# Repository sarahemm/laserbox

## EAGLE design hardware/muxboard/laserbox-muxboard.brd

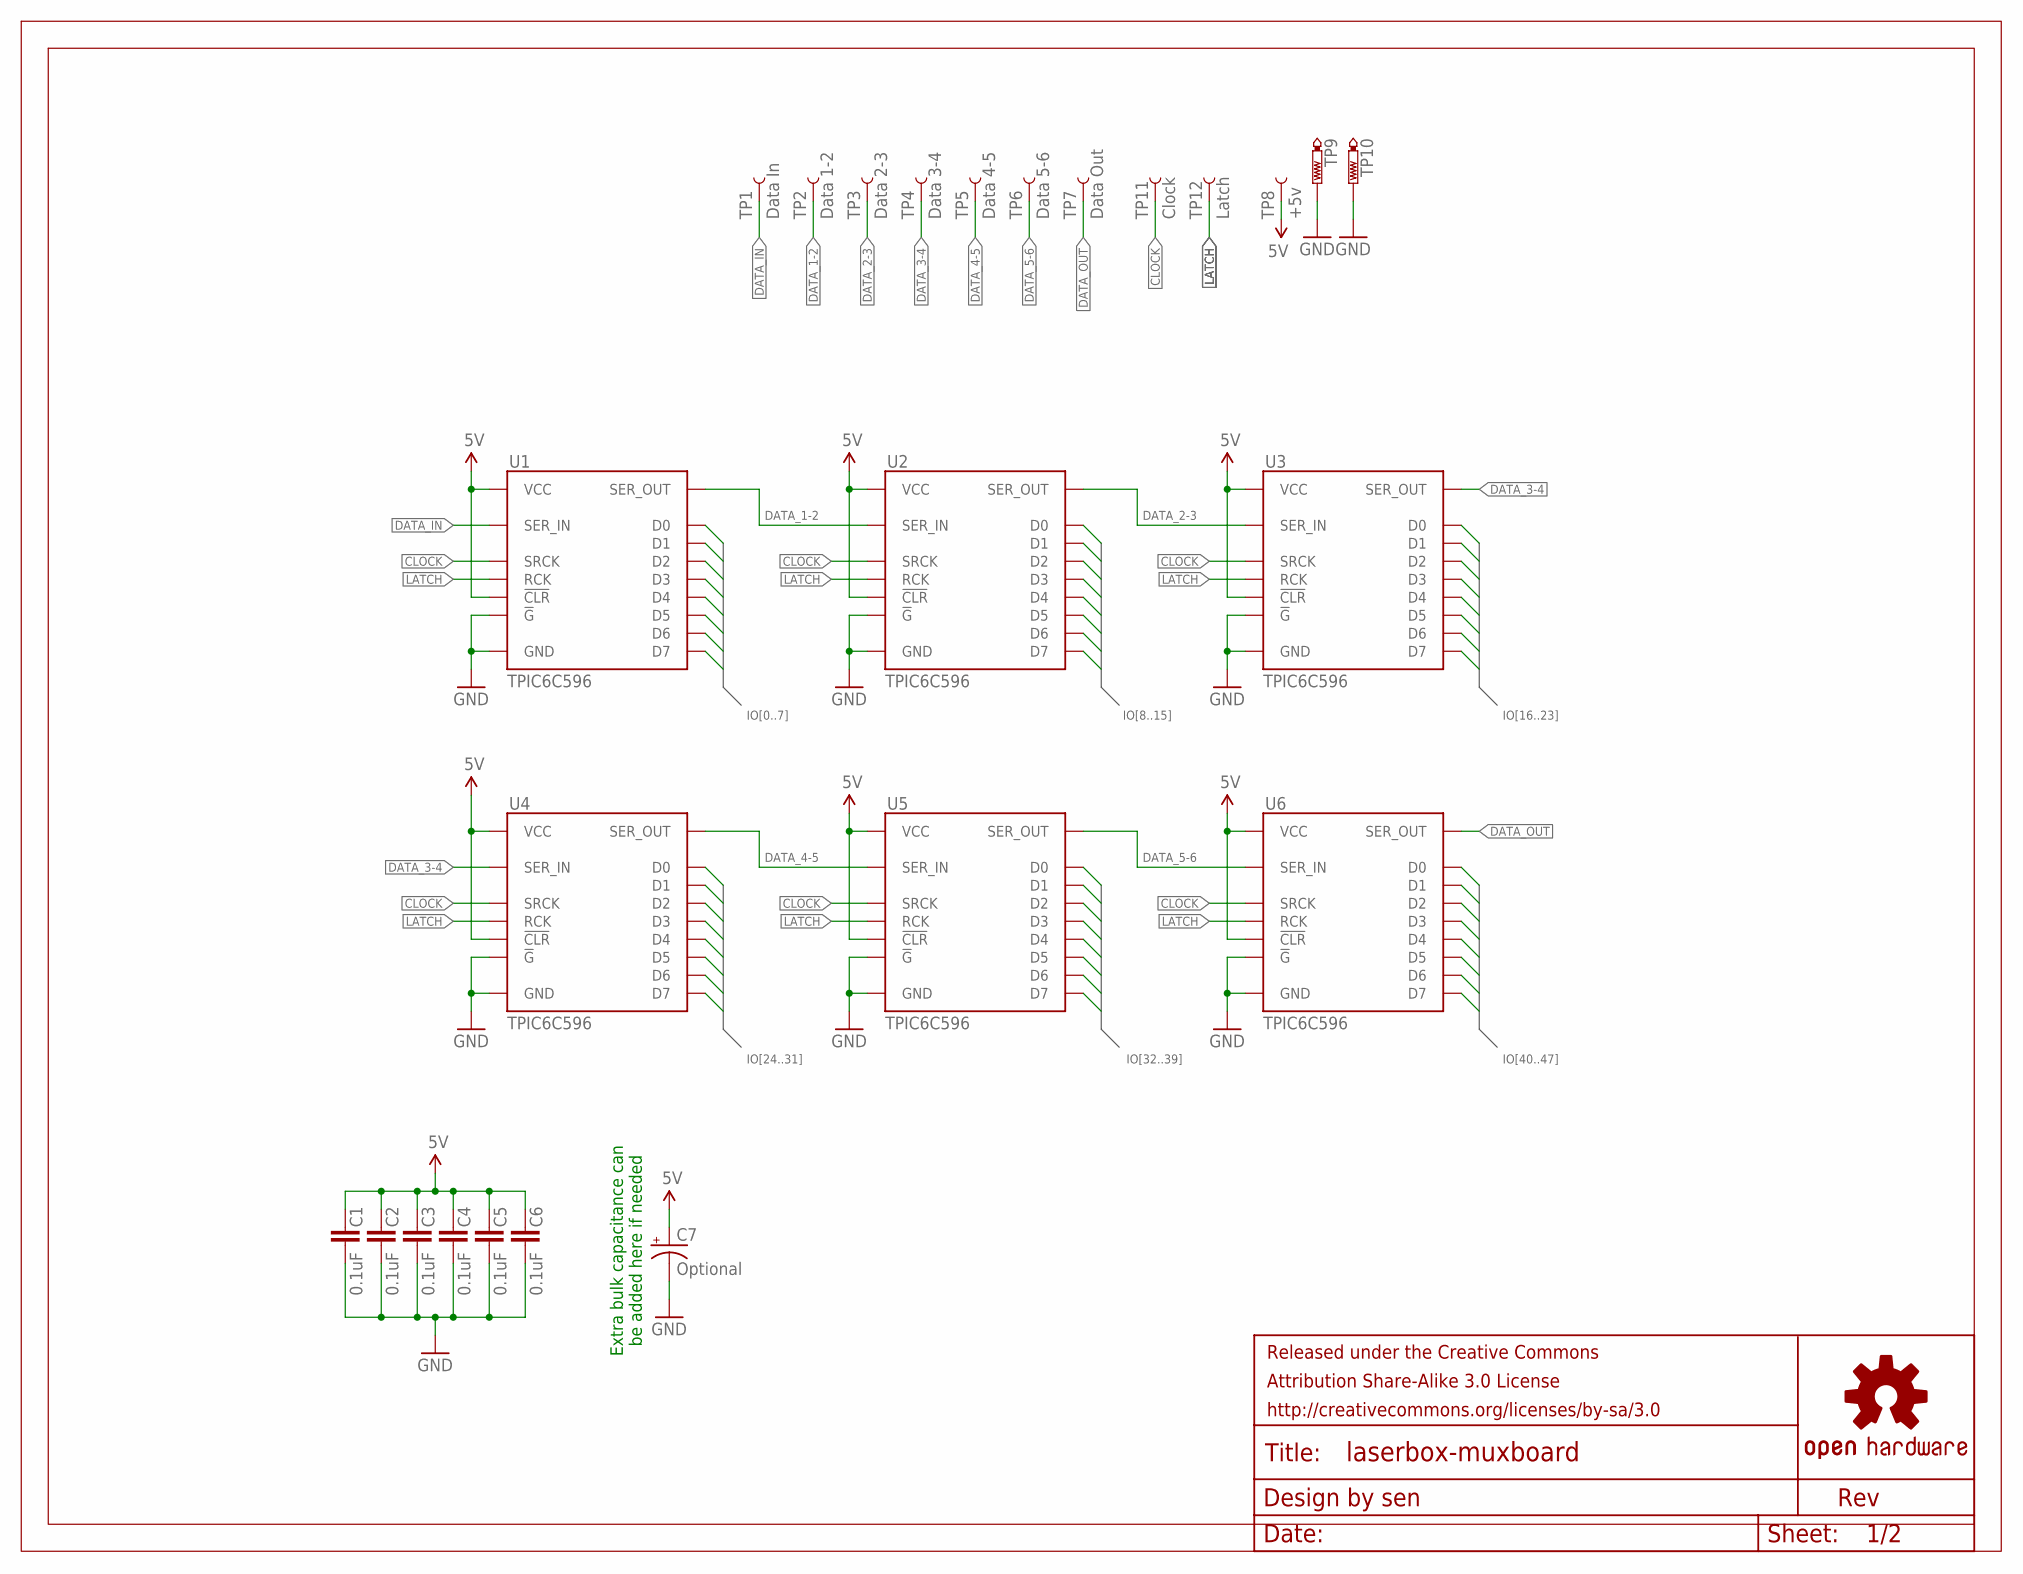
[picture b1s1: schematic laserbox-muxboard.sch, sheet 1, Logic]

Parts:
C1, C2, C3, C4, C5, C6: 0.1uF; 0603-CAP
C7: Optional; CPOL-RADIAL-10UF-25V
FRAME1: FRAME-LETTER-GRID-OSHW-SENOSHW-LOGO-L; OSHW-LOGO-L
TP1: Data In; PAD.03X.05
TP2: Data 1-2; PAD.03X.05
TP3: Data 2-3; PAD.03X.05
TP4: Data 3-4; PAD.03X.05
TP5: Data 4-5; PAD.03X.05
TP6: Data 5-6; PAD.03X.05
TP7: Data Out; PAD.03X.05
TP8: +5v; PAD.03X.05
TP9, TP10: GND; P1-13
TP11: Clock; PAD.03X.05
TP12: Latch; PAD.03X.05
U1, U2, U3, U4, U5, U6: TPIC6C596; SO016

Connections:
5V: C1.1, C2.1, C3.1, C4.1, C5.1, C6.1, C7.1 (+), TP8.P$1, U1.1 (VCC), U1.7 (!CLR), U2.1 (VCC), U2.7 (!CLR), U3.1 (VCC), U3.7 (!CLR), U4.1 (VCC), U4.7 (!CLR), U5.1 (VCC), U5.7 (!CLR), U6.1 (VCC), U6.7 (!CLR); also elsewhere on the board
CLOCK: TP11.P$1, U1.15 (SRCK), U2.15 (SRCK), U3.15 (SRCK), U4.15 (SRCK), U5.15 (SRCK), U6.15 (SRCK); also elsewhere on the board
DATA_1-2: TP2.P$1, U1.9 (SER_OUT), U2.2 (SER_IN)
DATA_2-3: TP3.P$1, U2.9 (SER_OUT), U3.2 (SER_IN)
DATA_3-4: TP4.P$1, U3.9 (SER_OUT), U4.2 (SER_IN)
DATA_4-5: TP5.P$1, U4.9 (SER_OUT), U5.2 (SER_IN)
DATA_5-6: TP6.P$1, U5.9 (SER_OUT), U6.2 (SER_IN)
DATA_IN: TP1.P$1, U1.2 (SER_IN); also elsewhere on the board
DATA_OUT: TP7.P$1, U6.9 (SER_OUT); also elsewhere on the board
GND: C1.2, C2.2, C3.2, C4.2, C5.2, C6.2, C7.2 (-), TP9.TP, TP10.TP, U1.8 (!G), U1.16 (GND), U2.8 (!G), U2.16 (GND), U3.8 (!G), U3.16 (GND), U4.8 (!G), U4.16 (GND), U5.8 (!G), U5.16 (GND), U6.8 (!G), U6.16 (GND); also elsewhere on the board
IO0: U1.3 (D0); also elsewhere on the board
IO1: U1.4 (D1); also elsewhere on the board
IO2: U1.5 (D2); also elsewhere on the board
IO3: U1.6 (D3); also elsewhere on the board
IO4: U1.11 (D4); also elsewhere on the board
IO5: U1.12 (D5); also elsewhere on the board
IO6: U1.13 (D6); also elsewhere on the board
IO7: U1.14 (D7); also elsewhere on the board
IO8: U2.3 (D0); also elsewhere on the board
IO9: U2.4 (D1); also elsewhere on the board
IO10: U2.5 (D2); also elsewhere on the board
IO11: U2.6 (D3); also elsewhere on the board
IO12: U2.11 (D4); also elsewhere on the board
IO13: U2.12 (D5); also elsewhere on the board
IO14: U2.13 (D6); also elsewhere on the board
IO15: U2.14 (D7); also elsewhere on the board
IO16: U3.3 (D0); also elsewhere on the board
IO17: U3.4 (D1); also elsewhere on the board
IO18: U3.5 (D2); also elsewhere on the board
IO19: U3.6 (D3); also elsewhere on the board
IO20: U3.11 (D4); also elsewhere on the board
IO21: U3.12 (D5); also elsewhere on the board
IO22: U3.13 (D6); also elsewhere on the board
IO23: U3.14 (D7); also elsewhere on the board
IO24: U4.3 (D0); also elsewhere on the board
IO25: U4.4 (D1); also elsewhere on the board
IO26: U4.5 (D2); also elsewhere on the board
IO27: U4.6 (D3); also elsewhere on the board
IO28: U4.11 (D4); also elsewhere on the board
IO29: U4.12 (D5); also elsewhere on the board
IO30: U4.13 (D6); also elsewhere on the board
IO31: U4.14 (D7); also elsewhere on the board
IO32: U5.3 (D0); also elsewhere on the board
IO33: U5.4 (D1); also elsewhere on the board
IO34: U5.5 (D2); also elsewhere on the board
IO35: U5.6 (D3); also elsewhere on the board
IO36: U5.11 (D4); also elsewhere on the board
IO37: U5.12 (D5); also elsewhere on the board
IO38: U5.13 (D6); also elsewhere on the board
IO39: U5.14 (D7); also elsewhere on the board
IO40: U6.3 (D0); also elsewhere on the board
IO41: U6.4 (D1); also elsewhere on the board
IO42: U6.5 (D2); also elsewhere on the board
IO43: U6.6 (D3); also elsewhere on the board
IO44: U6.11 (D4); also elsewhere on the board
IO45: U6.12 (D5); also elsewhere on the board
IO46: U6.13 (D6); also elsewhere on the board
IO47: U6.14 (D7); also elsewhere on the board
LATCH: TP12.P$1, U1.10 (RCK), U2.10 (RCK), U3.10 (RCK), U4.10 (RCK), U5.10 (RCK), U6.10 (RCK); also elsewhere on the board

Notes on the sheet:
Extra bulk capacitance can be added here if needed

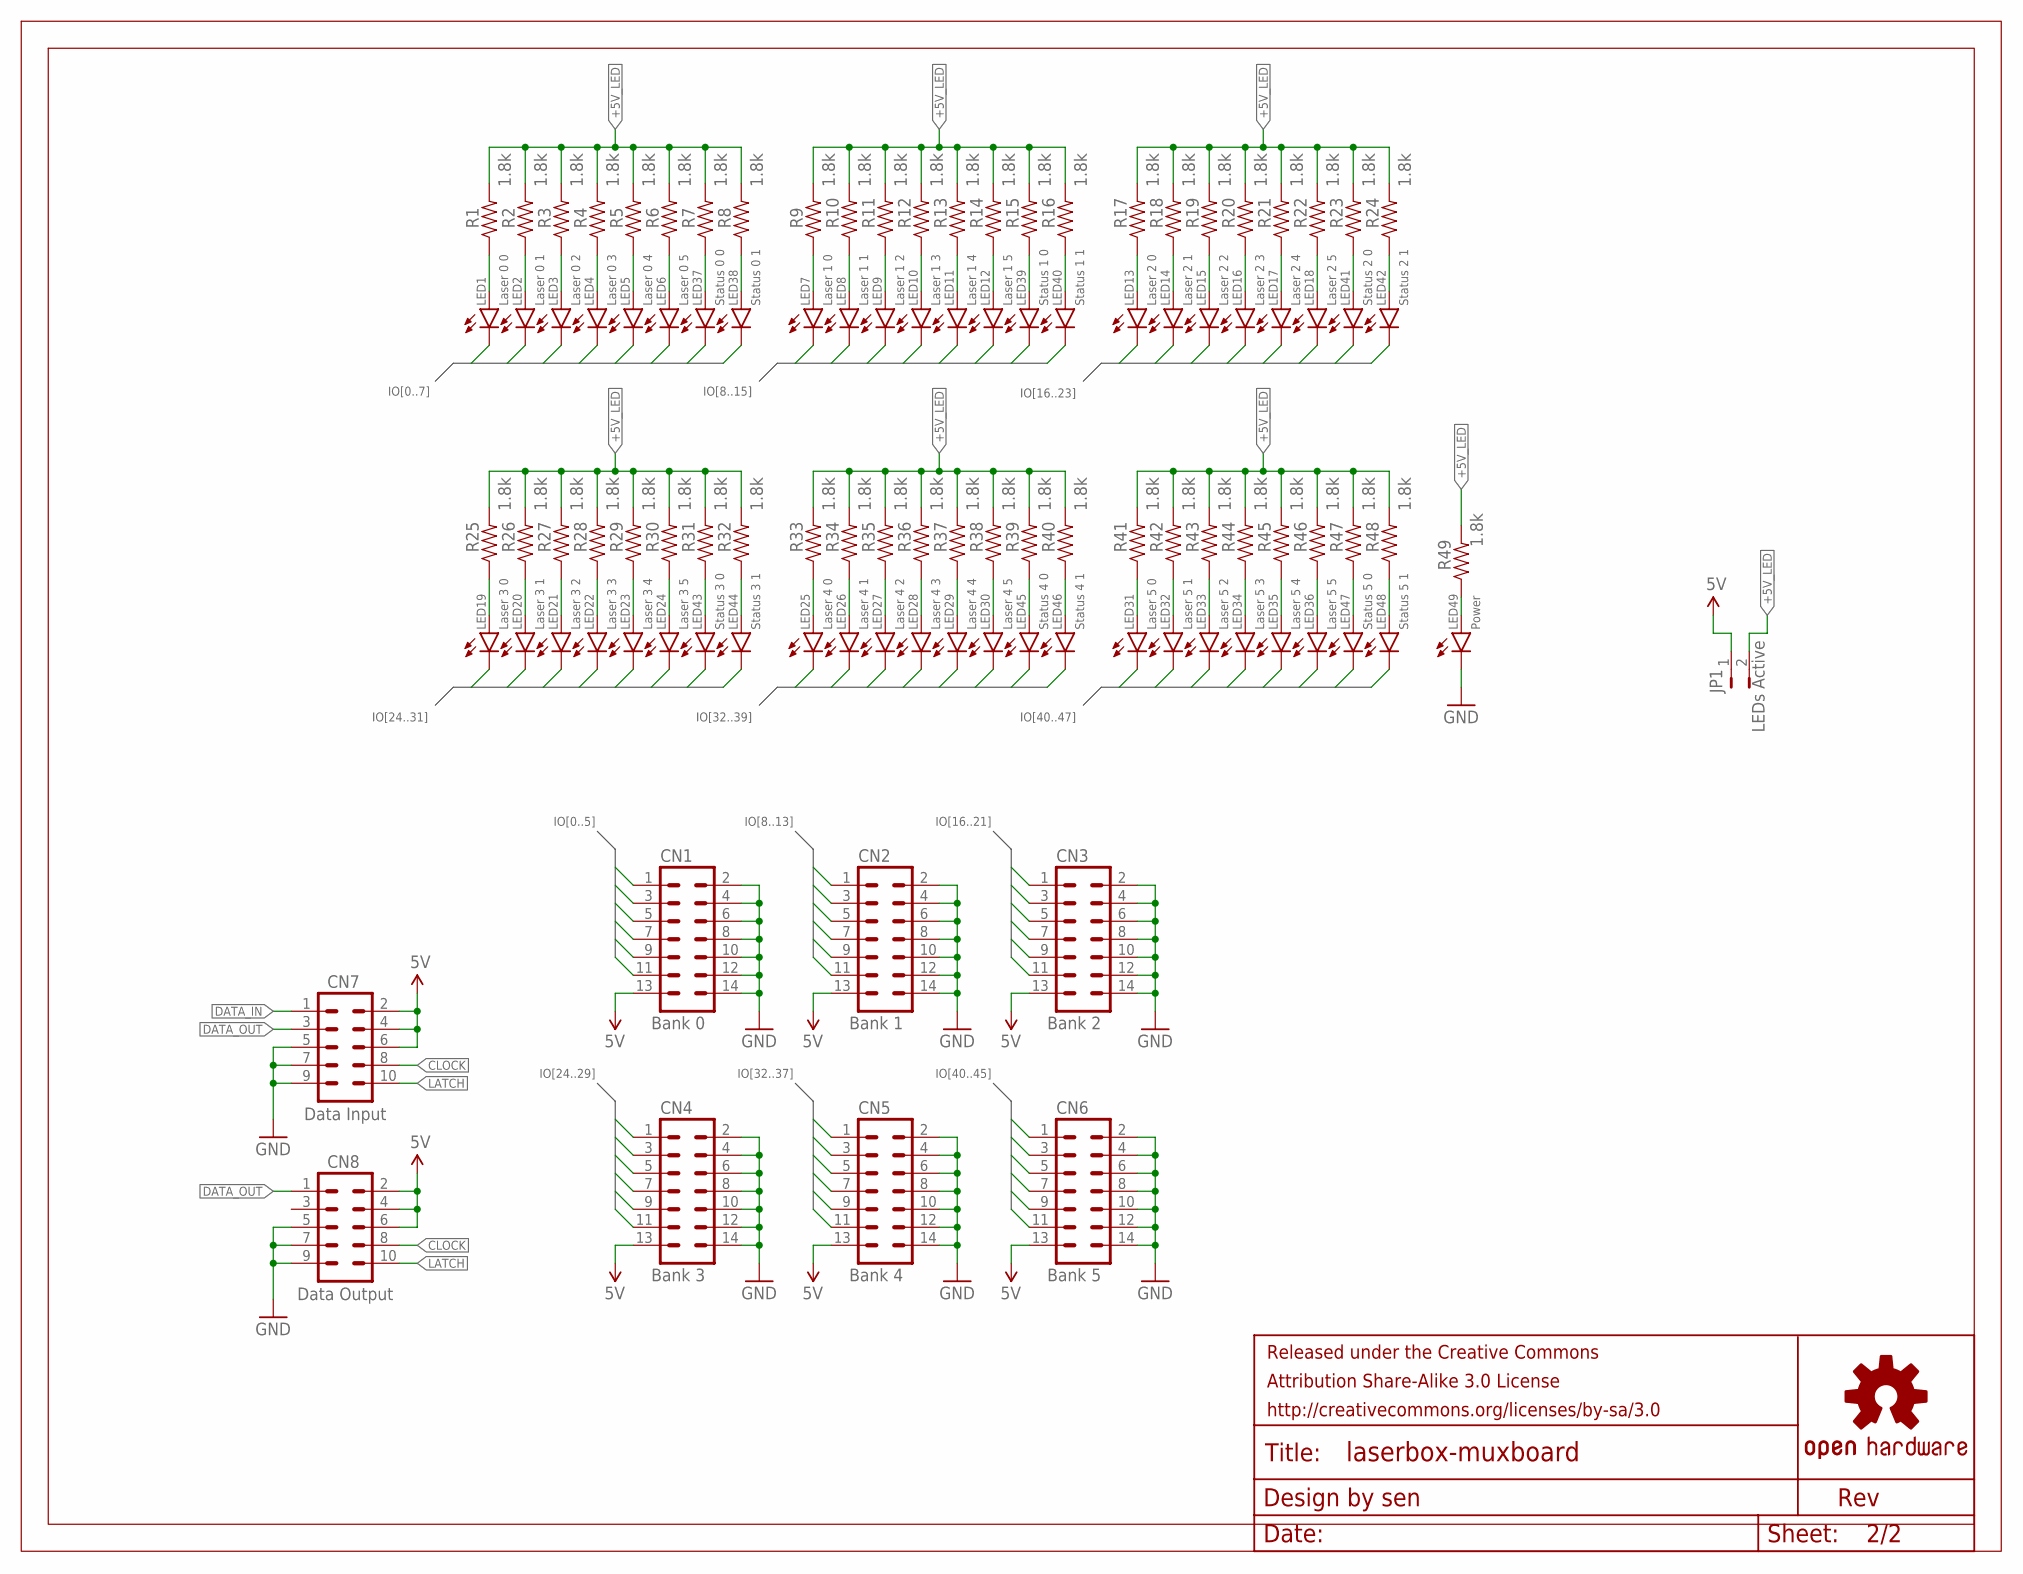
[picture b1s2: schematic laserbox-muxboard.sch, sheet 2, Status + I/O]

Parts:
CN1: Bank 0; 2X7-SHROUDED_LOCK
CN2: Bank 1; 2X7-SHROUDED_LOCK
CN3: Bank 2; 2X7-SHROUDED_LOCK
CN4: Bank 3; 2X7-SHROUDED_LOCK
CN5: Bank 4; 2X7-SHROUDED_LOCK
CN6: Bank 5; 2X7-SHROUDED_LOCK
CN7: Data Input; 2X5-SHROUDED_LOCK
CN8: Data Output; 2X5-SHROUDED_LOCK
FRAME2: FRAME-LETTER-GRID-OSHW-SENOSHW-LOGO-L; OSHW-LOGO-L
JP1: LEDs Active; PTH-JUMPER-2-NO_NO_SILK
LED1: Laser 0 0; LED3MM
LED2: Laser 0 1; LED3MM
LED3: Laser 0 2; LED3MM
LED4: Laser 0 3; LED3MM
LED5: Laser 0 4; LED3MM
LED6: Laser 0 5; LED3MM
LED7: Laser 1 0; LED3MM
LED8: Laser 1 1; LED3MM
LED9: Laser 1 2; LED3MM
LED10: Laser 1 3; LED3MM
LED11: Laser 1 4; LED3MM
LED12: Laser 1 5; LED3MM
LED13: Laser 2 0; LED3MM
LED14: Laser 2 1; LED3MM
LED15: Laser 2 2; LED3MM
LED16: Laser 2 3; LED3MM
LED17: Laser 2 4; LED3MM
LED18: Laser 2 5; LED3MM
LED19: Laser 3 0; LED3MM
LED20: Laser 3 1; LED3MM
LED21: Laser 3 2; LED3MM
LED22: Laser 3 3; LED3MM
LED23: Laser 3 4; LED3MM
LED24: Laser 3 5; LED3MM
LED25: Laser 4 0; LED3MM
LED26: Laser 4 1; LED3MM
LED27: Laser 4 2; LED3MM
LED28: Laser 4 3; LED3MM
LED29: Laser 4 4; LED3MM
LED30: Laser 4 5; LED3MM
LED31: Laser 5 0; LED3MM
LED32: Laser 5 1; LED3MM
LED33: Laser 5 2; LED3MM
LED34: Laser 5 3; LED3MM
LED35: Laser 5 4; LED3MM
LED36: Laser 5 5; LED3MM
LED37: Status 0 0; LED3MM
LED38: Status 0 1; LED3MM
LED39: Status 1 0; LED3MM
LED40: Status 1 1; LED3MM
LED41: Status 2 0; LED3MM
LED42: Status 2 1; LED3MM
LED43: Status 3 0; LED3MM
LED44: Status 3 1; LED3MM
LED45: Status 4 0; LED3MM
LED46: Status 4 1; LED3MM
LED47: Status 5 0; LED3MM
LED48: Status 5 1; LED3MM
LED49: Power; LED3MM
R1, R2, R3, R4, R5, R6, R7, R8, R9, R10, R11, R12, R13, R14, R15, R16, R17, R18, R19, R20, R21, R22, R23, R24, R25, R26, R27, R28, R29, R30, R31, R32, R33, R34, R35, R36, R37, R38, R39, R40, R41, R42, R43, R44, R45, R46, R47, R48, R49: 1.8k; 0603-RES

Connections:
5V: CN1.13, CN2.13, CN3.13, CN4.13, CN5.13, CN6.13, CN7.2, CN7.4, CN7.6, CN8.2, CN8.4, CN8.6, JP1.1; also elsewhere on the board
+5V_LED: JP1.2, R1.2, R2.2, R3.2, R4.2, R5.2, R6.2, R7.2, R8.2, R9.2, R10.2, R11.2, R12.2, R13.2, R14.2, R15.2, R16.2, R17.2, R18.2, R19.2, R20.2, R21.2, R22.2, R23.2, R24.2, R25.2, R26.2, R27.2, R28.2, R29.2, R30.2, R31.2, R32.2, R33.2, R34.2, R35.2, R36.2, R37.2, R38.2, R39.2, R40.2, R41.2, R42.2, R43.2, R44.2, R45.2, R46.2, R47.2, R48.2, R49.2
CLOCK: CN7.8, CN8.8; also elsewhere on the board
DATA_IN: CN7.1; also elsewhere on the board
DATA_OUT: CN7.3, CN8.1; also elsewhere on the board
GND: CN1.2, CN1.4, CN1.6, CN1.8, CN1.10, CN1.12, CN1.14, CN2.2, CN2.4, CN2.6, CN2.8, CN2.10, CN2.12, CN2.14, CN3.2, CN3.4, CN3.6, CN3.8, CN3.10, CN3.12, CN3.14, CN4.2, CN4.4, CN4.6, CN4.8, CN4.10, CN4.12, CN4.14, CN5.2, CN5.4, CN5.6, CN5.8, CN5.10, CN5.12, CN5.14, CN6.2, CN6.4, CN6.6, CN6.8, CN6.10, CN6.12, CN6.14, CN7.5, CN7.7, CN7.9, CN8.5, CN8.7, CN8.9, LED49.K (C); also elsewhere on the board
IO0: CN1.1, LED1.K (C); also elsewhere on the board
IO1: CN1.3, LED2.K (C); also elsewhere on the board
IO2: CN1.5, LED3.K (C); also elsewhere on the board
IO3: CN1.7, LED4.K (C); also elsewhere on the board
IO4: CN1.9, LED5.K (C); also elsewhere on the board
IO5: CN1.11, LED6.K (C); also elsewhere on the board
IO6: LED37.K (C); also elsewhere on the board
IO7: LED38.K (C); also elsewhere on the board
IO8: CN2.1, LED7.K (C); also elsewhere on the board
IO9: CN2.3, LED8.K (C); also elsewhere on the board
IO10: CN2.5, LED9.K (C); also elsewhere on the board
IO11: CN2.7, LED10.K (C); also elsewhere on the board
IO12: CN2.9, LED11.K (C); also elsewhere on the board
IO13: CN2.11, LED12.K (C); also elsewhere on the board
IO14: LED39.K (C); also elsewhere on the board
IO15: LED40.K (C); also elsewhere on the board
IO16: CN3.1, LED13.K (C); also elsewhere on the board
IO17: CN3.3, LED14.K (C); also elsewhere on the board
IO18: CN3.5, LED15.K (C); also elsewhere on the board
IO19: CN3.7, LED16.K (C); also elsewhere on the board
IO20: CN3.9, LED17.K (C); also elsewhere on the board
IO21: CN3.11, LED18.K (C); also elsewhere on the board
IO22: LED41.K (C); also elsewhere on the board
IO23: LED42.K (C); also elsewhere on the board
IO24: CN4.1, LED19.K (C); also elsewhere on the board
IO25: CN4.3, LED20.K (C); also elsewhere on the board
IO26: CN4.5, LED21.K (C); also elsewhere on the board
IO27: CN4.7, LED22.K (C); also elsewhere on the board
IO28: CN4.9, LED23.K (C); also elsewhere on the board
IO29: CN4.11, LED24.K (C); also elsewhere on the board
IO30: LED43.K (C); also elsewhere on the board
IO31: LED44.K (C); also elsewhere on the board
IO32: CN5.1, LED25.K (C); also elsewhere on the board
IO33: CN5.3, LED26.K (C); also elsewhere on the board
IO34: CN5.5, LED27.K (C); also elsewhere on the board
IO35: CN5.7, LED28.K (C); also elsewhere on the board
IO36: CN5.9, LED29.K (C); also elsewhere on the board
IO37: CN5.11, LED30.K (C); also elsewhere on the board
IO38: LED45.K (C); also elsewhere on the board
IO39: LED46.K (C); also elsewhere on the board
IO40: CN6.1, LED31.K (C); also elsewhere on the board
IO41: CN6.3, LED32.K (C); also elsewhere on the board
IO42: CN6.5, LED33.K (C); also elsewhere on the board
IO43: CN6.7, LED34.K (C); also elsewhere on the board
IO44: CN6.9, LED35.K (C); also elsewhere on the board
IO45: CN6.11, LED36.K (C); also elsewhere on the board
IO46: LED47.K (C); also elsewhere on the board
IO47: LED48.K (C); also elsewhere on the board
LATCH: CN7.10, CN8.10; also elsewhere on the board
LED1_R: LED1.A, R1.1
LED2_R: LED2.A, R2.1
LED3_R: LED3.A, R3.1
LED4_R: LED4.A, R4.1
LED5_R: LED5.A, R5.1
LED6_R: LED6.A, R6.1
LED7_R: LED7.A, R9.1
LED8_R: LED8.A, R10.1
LED9_R: LED9.A, R11.1
LED10_R: LED10.A, R12.1
LED11_R: LED11.A, R13.1
LED12_R: LED12.A, R14.1
LED13_R: LED13.A, R17.1
LED14_R: LED14.A, R18.1
LED15_R: LED15.A, R19.1
LED16_R: LED16.A, R20.1
LED17_R: LED17.A, R21.1
LED18_R: LED18.A, R22.1
LED19_R: LED19.A, R25.1
LED20_R: LED20.A, R26.1
LED21_R: LED21.A, R27.1
LED22_R: LED22.A, R28.1
LED23_R: LED23.A, R29.1
LED24_R: LED24.A, R30.1
LED25_R: LED25.A, R33.1
LED26_R: LED26.A, R34.1
LED27_R: LED27.A, R35.1
LED28_R: LED28.A, R36.1
LED29_R: LED29.A, R37.1
LED30_R: LED30.A, R38.1
LED31_R: LED31.A, R41.1
LED32_R: LED32.A, R42.1
LED33_R: LED33.A, R43.1
LED34_R: LED34.A, R44.1
LED35_R: LED35.A, R45.1
LED36_R: LED36.A, R46.1
LED37_R: LED37.A, R7.1
LED38_R: LED38.A, R8.1
LED39_R: LED39.A, R15.1
LED40_R: LED40.A, R16.1
LED41_R: LED41.A, R23.1
LED42_R: LED42.A, R24.1
LED43_R: LED43.A, R31.1
LED44_R: LED44.A, R32.1
LED45_R: LED45.A, R39.1
LED46_R: LED46.A, R40.1
LED47_R: LED47.A, R47.1
LED48_R: LED48.A, R48.1
LED49_R: LED49.A, R49.1

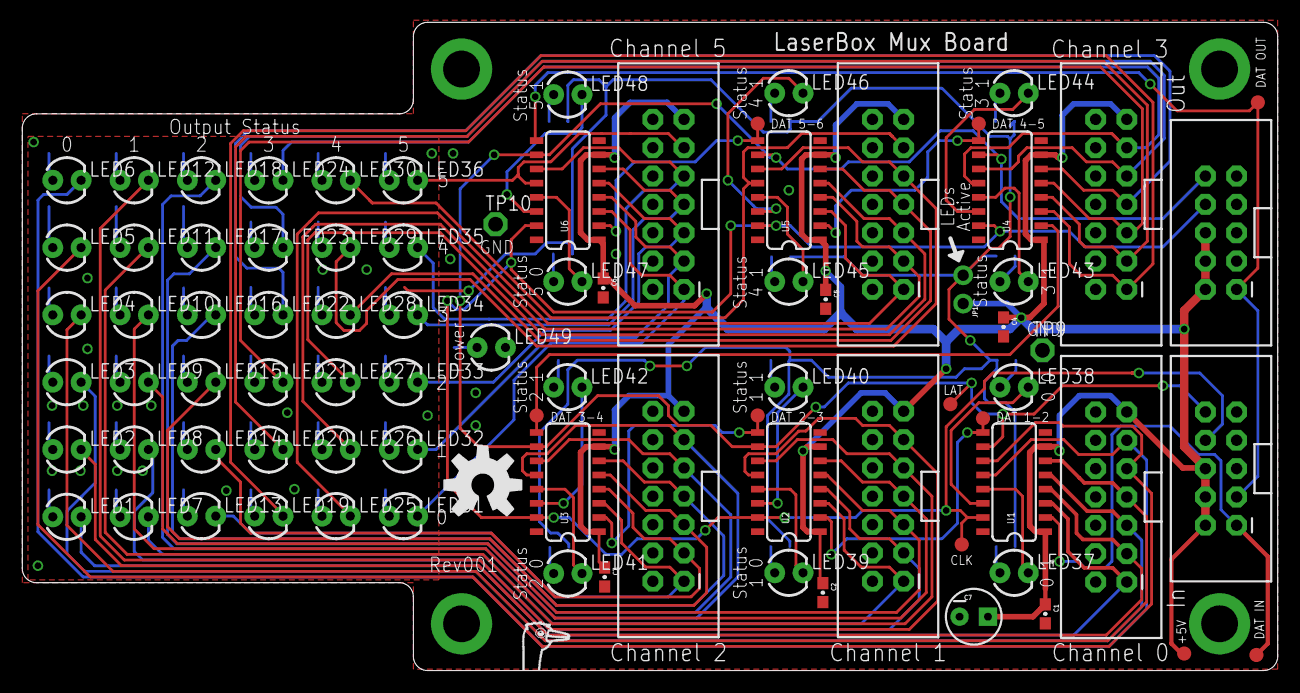
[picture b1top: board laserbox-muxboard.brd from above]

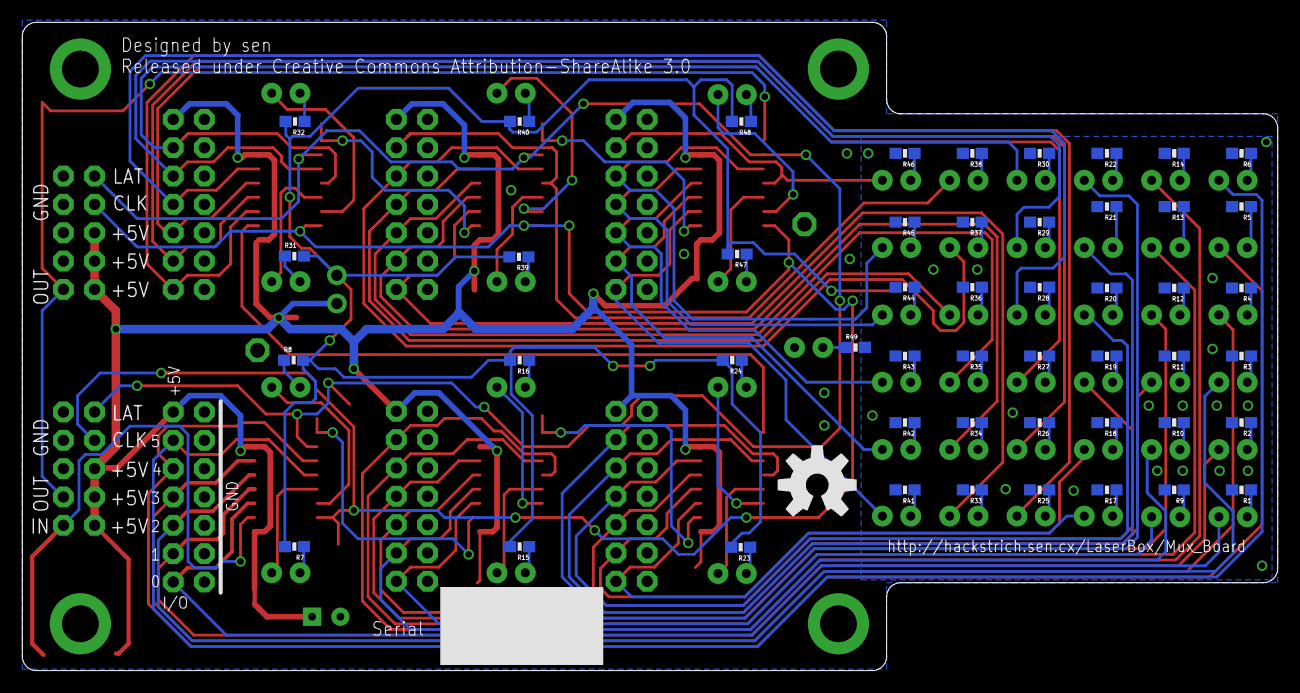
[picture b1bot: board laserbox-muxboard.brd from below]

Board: 2 copper layers, 112.5 x 58.1 mm, 135 parts (50 on the bottom side), 109 nets.

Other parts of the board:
U$1: STRICH-LOGO-R

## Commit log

2017-01-18 Adding current 3D model of the laserbox project.
2017-01-18 Added gesture sensor opening.
2017-01-18 Splitting out animation data into separate files.
2017-01-27 Completed and checklisted LaserBox Mux Board Rev001.
2017-01-28 Adding start at a board layout.
2017-01-29 Routing continues.
2017-01-29 Commit before I try changing the data connectors around.
2017-01-29 Routing continues, 27 airwires left, almost entirely 5V/5V_LED.
2017-01-30 Routing continues, 9 airwires left to route.
2017-01-30 Board routing and checklist complete.
2017-03-04 Adding checklisted CAM files.
2017-03-04 Adding laser cut test plate design file.
2017-03-16 Adding complete/working LaserBox animation pattern editor.
2017-03-19 Filename is configurable now, removing TODO.
2017-03-19 Mid-work on ability to attach to a live LaserBox and display changes in real time.
2017-03-19 Finished feature to attach to live LaserBox, now works on both planes.
2017-03-19 Reorganized pixel layout internally to match hardware.
    Previously the pixel array was [y][x] but hardware uses [x][y] internally.
    Changed this to match, and also DRYed out the live set_plane_from_plane now that they match.
2017-03-22 Added ability to export to Pattern v2 format.
    Can now save as v1 or export to v2, but only load v1 currently.
    Eventually would be nice to eliminate v1 altogether but not really required.
2017-03-22 Fixing export message to report when done.
2017-04-02 New frame now starts with copy of previously selected frame.
2017-04-02 Added command to reverse animation sequence.
2017-04-02 Implemented importing Pattern v2 (LBP) files into the editor!
2017-04-04 Adding current version of the firmware, is a work in progress but functional.
2017-04-04 Moving the test file to a separate directory to make it clear it's not part of the final project.
2017-04-05 Work-in-progress laser cut part designs for the structure.
2017-04-06 Completed first revision of all the laser cut parts.
    Most of these probably still need major work, but it's a start.
2017-04-06 Added material amounts to each file. ~40 square feet total, yikes!
2017-04-07 Added Fog subsystem, currently just supports a fan test.
2017-04-14 Fog code improvements after first integration test. Still messy.
2017-04-15 Changing live mode to be compatible w/ new debug UI firmware.
2017-04-15 Debug subsystem overhauled to use a hierarchial menu rather than single-byte commands.
2017-04-15 Added laser sequence test and ability to set clock.
2017-04-15 Removing test motion code from last commit.
2017-04-15 Added skeleton of config subsystem.
2017-04-16 Renamed storageGetPattern to storageGetFileContents as there's nothing pattern-specific about it.
2017-04-16 Simple configuration subsystem now in place and working.
2017-04-18 Split out left/right vert rails into separate files to increase packing efficiency on panels.
2017-04-18 Adding notes on what each directory is for.
2017-04-18 Adding material usage planning file.

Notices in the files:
hardware/muxboard/laserbox-muxboard.brd:
Released under Creative Commons Attribution-ShareAlike 3.0
parts and their libraries:
SparkFun-DigitalIC: Licensing: Creative Commons ShareAlike 4.0 International - https://creativecommons.org/licenses/by-sa/4.0
logos-sen: Released under the Creative Commons Attribution Share-Alike 3.0 License
logos-sen: http://creativecommons.org/licenses/by-sa/3.0
